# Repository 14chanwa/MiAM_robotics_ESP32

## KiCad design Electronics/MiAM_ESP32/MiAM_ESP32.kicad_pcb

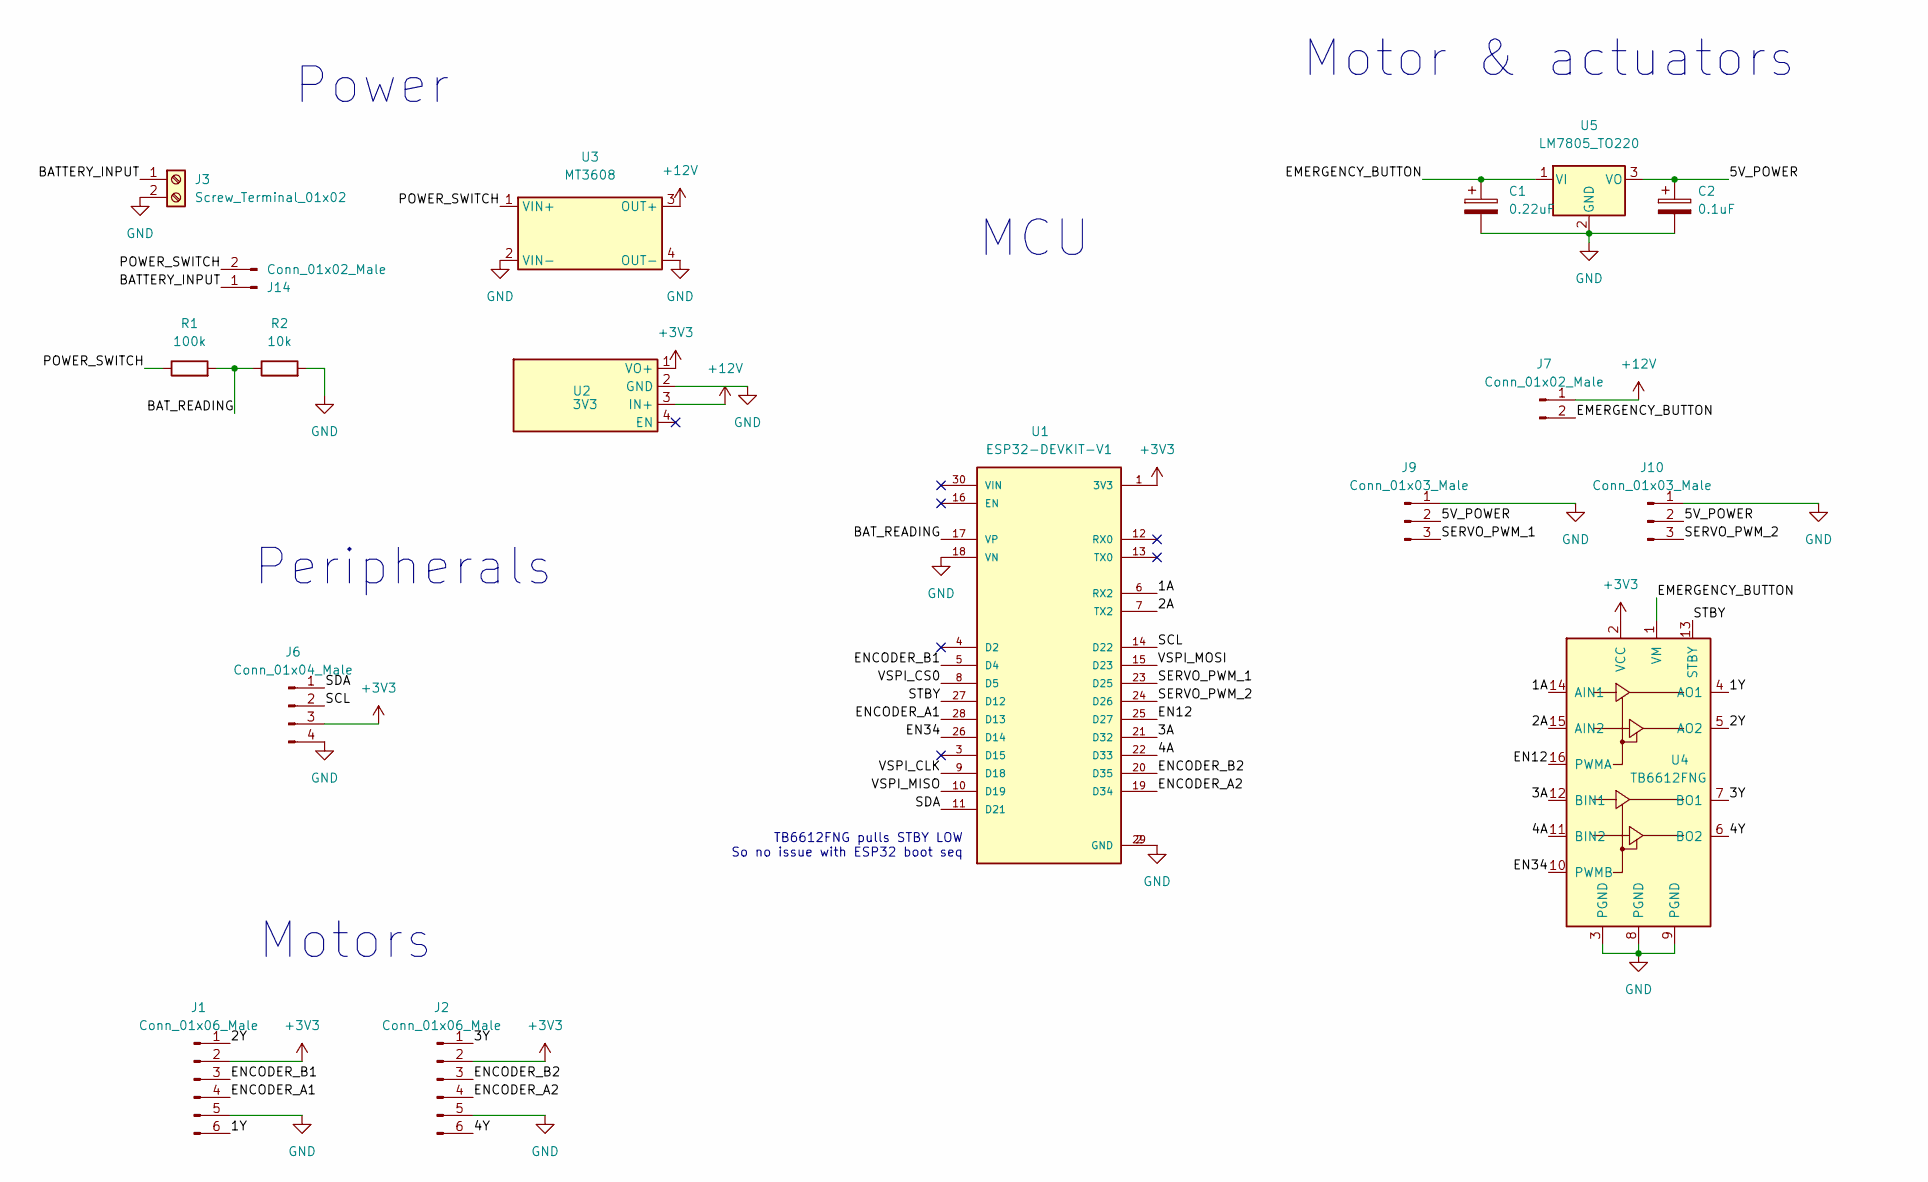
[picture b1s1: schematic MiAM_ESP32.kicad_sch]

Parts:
C1: 0.22uF; CP_Radial_D4.0mm_P2.00mm
C2: 0.1uF; CP_Radial_Tantal_D5.0mm_P5.00mm
J1, J2: Conn_01x06_Male; PinHeader_1x06_P2.54mm_Vertical
J3: Screw_Terminal_01x02; JST_PH_B2B-PH-K_1x02_P2.00mm_Vertical
J6: Conn_01x04_Male; PinHeader_1x04_P2.54mm_Vertical
J7, J14: Conn_01x02_Male; PinHeader_1x02_P2.54mm_Vertical
J9, J10: Conn_01x03_Male; PinHeader_1x03_P2.54mm_Vertical
R1: 100k; R_Axial_DIN0309_L9.0mm_D3.2mm_P12.70mm_Horizontal
R2: 10k; R_Axial_DIN0309_L9.0mm_D3.2mm_P12.70mm_Horizontal
U1: ESP32-DEVKIT-V1; MODULE_ESP32_DEVKIT_V1; PARTREV N/A
U2: 3V3; VoltageRegulator
U3: MT3608
U4: TB6612FNG
U5: LM7805_TO220; TO-220-3_Vertical

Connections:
+3V3: J1.2, J2.2, J6.3, U1.1 (3V3), U2.1 (VO+), U4.2 (VCC)
+12V: J7.1, U2.3 (IN+), U3.3 (OUT+)
/1A: U1.6 (RX2), U4.14 (AIN1)
/1Y: J1.6, U4.4 (AO1)
/2A: U1.7 (TX2), U4.15 (AIN2)
/2Y: J1.1, U4.5 (AO2)
/3A: U1.21 (D32), U4.12 (BIN1)
/3Y: J2.1, U4.7 (BO1)
/4A: U1.22 (D33), U4.11 (BIN2)
/4Y: J2.6, U4.6 (BO2)
/5V_POWER: C2.1, J9.2, J10.2, U5.3 (VO)
/BATTERY_INPUT: J3.1, J14.1
/BAT_READING: R1.2, R2.1, U1.17 (VP)
/EMERGENCY_BUTTON: C1.1, J7.2, U4.1 (VM), U5.1 (VI)
/EN12: U1.25 (D27), U4.16 (PWMA)
/EN34: U1.26 (D14), U4.10 (PWMB)
/ENCODER_A1: J1.4, U1.28 (D13)
/ENCODER_A2: J2.4, U1.19 (D34)
/ENCODER_B1: J1.3, U1.5 (D4)
/ENCODER_B2: J2.3, U1.20 (D35)
/POWER_SWITCH: J14.2, R1.1, U3.1 (VIN+)
/SCL: J6.2, U1.14 (D22)
/SDA: J6.1, U1.11 (D21)
/SERVO_PWM_1: J9.3, U1.23 (D25)
/SERVO_PWM_2: J10.3, U1.24 (D26)
/STBY: U1.27 (D12), U4.13 (STBY)
/VSPI_CLK: U1.9 (D18)
/VSPI_CS0: U1.8 (D5)
/VSPI_MISO: U1.10 (D19)
/VSPI_MOSI: U1.15 (D23)
GND: C1.2, C2.2, J1.5, J2.5, J3.2, J6.4, J9.1, J10.1, R2.2, U1.2 (GND), U1.18 (VN), U1.29 (GND), U2.2 (GND), U3.2 (VIN-), U3.4 (OUT-), U4.3 (PGND), U4.8 (PGND), U4.9 (PGND), U5.2 (GND)

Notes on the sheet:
Motor & actuators
Power
TB6612FNG pulls STBY LOW So no issue with ESP32 boot seq
MCU
Motors
Peripherals

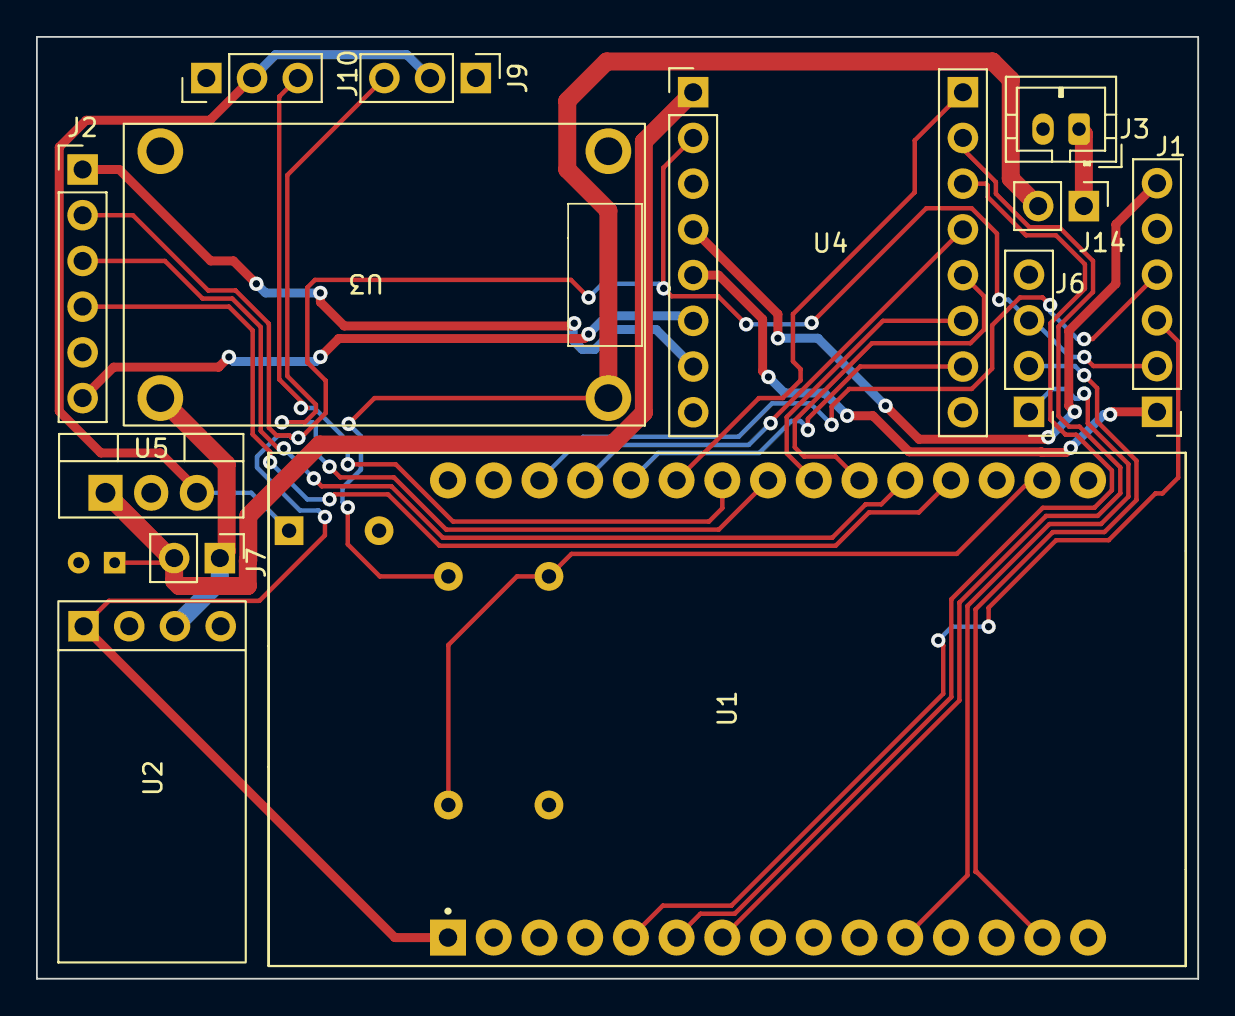
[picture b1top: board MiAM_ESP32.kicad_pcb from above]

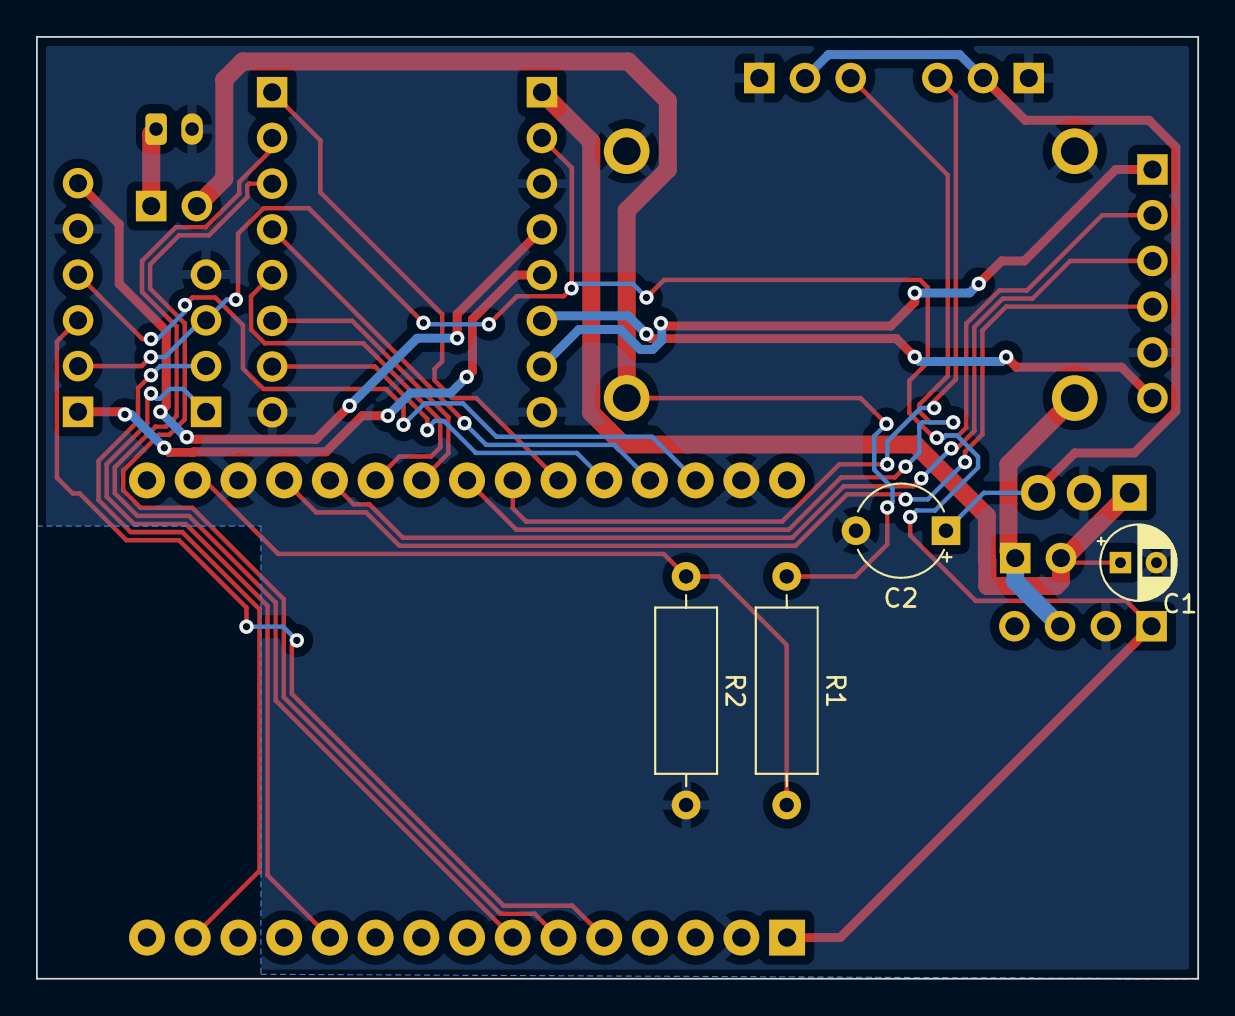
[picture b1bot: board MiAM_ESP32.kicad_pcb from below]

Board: 2 copper layers, 64.5 x 52.3 mm, 17 parts (4 on the bottom side), 27 nets.

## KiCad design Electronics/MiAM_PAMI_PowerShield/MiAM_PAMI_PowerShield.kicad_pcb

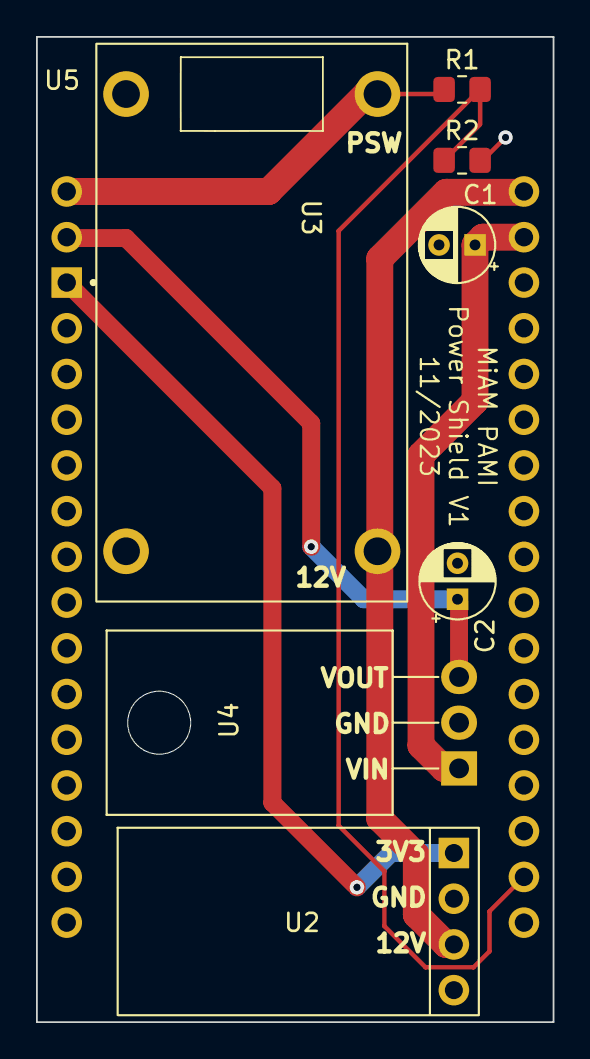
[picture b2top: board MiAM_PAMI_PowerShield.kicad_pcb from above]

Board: 2 copper layers, 28.7 x 54.7 mm, 8 parts (0 on the bottom side), 7 nets.

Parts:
C1: 0.22uF; CP_Radial_D4.0mm_P2.00mm
C2: 0.1uF; CP_Radial_D4.0mm_P2.00mm
R1: 100k; R_0805_2012Metric_Pad1.20x1.40mm_HandSolder
R2: 10k; R_0805_2012Metric_Pad1.20x1.40mm_HandSolder
U2: 3V3; VoltageRegulator
U3: MT3608
U4: LM7805_TO220; TO-220-3_Horizontal_TabDown
U5: ESP32-DEVKIT-V1; ESP32_ShieldPattern

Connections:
+3V3: U2.1 (VO+), U5.1 (3V3)
+12V: U2.3 (IN+), U3.3 (OUT+), U5.SH2 (12V)
/5V_POWER: C2.1, U4.3 (VO), U5.SH3 (SERVO_V)
/BAT_READING: R1.2, R2.1, U5.17 (VP)
/EMERGENCY_BUTTON: C1.1, U4.1 (VI), U5.SH1 (EMG_BUT)
/POWER_SWITCH: R1.1, U3.1 (VIN+), U5.SH4 (POW_SW)
GND: C1.2, C2.2, R2.2, U2.2 (GND), U3.2 (VIN-), U3.4 (OUT-), U4.2 (GND), U5.18 (VN), U5.29 (GND)

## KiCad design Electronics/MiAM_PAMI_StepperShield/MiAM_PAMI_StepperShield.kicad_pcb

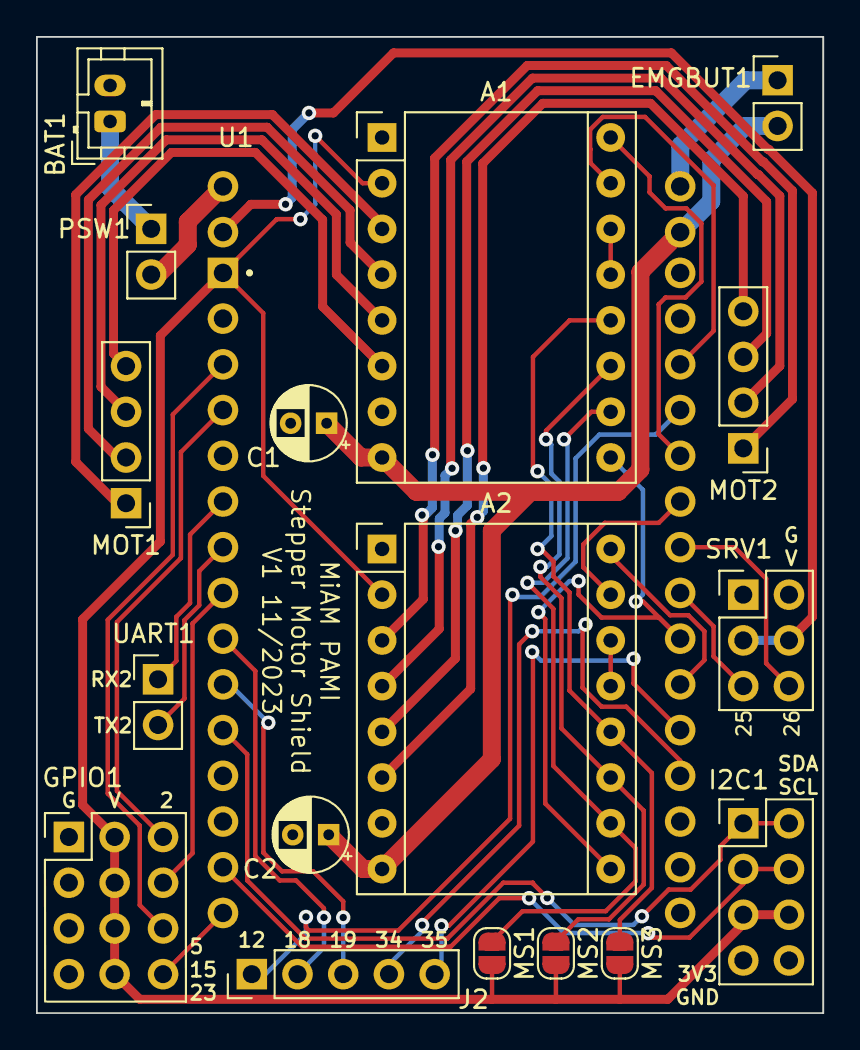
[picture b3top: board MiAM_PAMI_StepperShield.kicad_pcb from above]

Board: 2 copper layers, 43.7 x 54.2 mm, 18 parts (0 on the bottom side), 40 nets.

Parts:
A1, A2: Pololu_Breakout_A4988; Pololu_Breakout-16_15.2x20.3mm
BAT1: Screw_Terminal_01x02; JST_PH_B2B-PH-K_1x02_P2.00mm_Vertical
C1, C2: 100uF; CP_Radial_D4.0mm_P2.00mm
EMGBUT1: Conn_01x02_Male; PinHeader_1x02_P2.54mm_Vertical
GPIO1: PinHeader_3x4_P2.54mm_Vertical
I2C1: Conn_02x04_Odd_Even; PinHeader_2x04_P2.54mm_Vertical
J2: Conn_01x05_Male; PinHeader_1x05_P2.54mm_Vertical
MOT1, MOT2: Conn_01x04_Male; PinHeader_1x04_P2.54mm_Vertical
MS1, MS2, MS3: SolderJumper_2_Open; SolderJumper-2_P1.3mm_Open_RoundedPad1.0x1.5mm
PSW1: Conn_01x02_Male; PinHeader_1x02_P2.54mm_Vertical
SRV1: Conn_02x03_Odd_Even; PinHeader_2x03_P2.54mm_Vertical
U1: ESP32-DEVKIT-V1; ESP32_ShieldPattern
UART1: Conn_01x02_Male; PinHeader_1x02_P2.54mm_Vertical

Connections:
+3V3: A1.2 (VDD), A2.2 (VDD), GPIO1.5, GPIO1.6, GPIO1.7, GPIO1.8, I2C1.5, I2C1.6, MS1.2 (B), MS2.2 (B), MS3.2 (B), U1.1 (3V3)
+12V: EMGBUT1.1, U1.SH2 (12V)
/5V_POWER: SRV1.3, SRV1.4, U1.SH3 (SERVO_V)
/BATTERY_INPUT: BAT1.1, PSW1.1
/DIR_1: A1.16 (DIR), U1.26 (D14)
/DIR_2: A2.16 (DIR), U1.21 (D32)
/EMERGENCY_BUTTON: A1.8 (VMOT), A2.8 (VMOT), C1.1, C2.1, EMGBUT1.2, U1.SH1 (EMG_BUT)
/GPIO2: GPIO1.9, U1.4 (D2)
/GPIO5: GPIO1.10, U1.8 (D5)
/GPIO12: J2.1, U1.27 (D12)
/GPIO15: GPIO1.11, U1.3 (D15)
/GPIO18: J2.2, U1.9 (D18)
/GPIO19: J2.3, U1.10 (D19)
/GPIO23: GPIO1.12, U1.15 (D23)
/GPIO34: J2.4, U1.19 (D34)
/GPIO35: J2.5, U1.20 (D35)
/MS1: A1.10 (MS1), A2.10 (MS1), MS1.1 (A)
/MS2: A1.11 (MS2), A2.11 (MS2), MS2.1 (A)
/MS3: A1.12 (MS3), A2.12 (MS3), MS3.1 (A)
/NOT_MOT_EN: A1.9 (~ENABLE), A2.9 (~ENABLE), U1.22 (D33)
/POWER_SWITCH: PSW1.2, U1.SH4 (POW_SW)
/RX2: U1.6 (RX2), UART1.1
/SCL: I2C1.3, I2C1.4, U1.14 (D22)
/SDA: I2C1.1, I2C1.2, U1.11 (D21)
/SERVO_PWM_1: SRV1.5, U1.23 (D25)
/SERVO_PWM_2: SRV1.6, U1.24 (D26)
/STEP_1: A1.15 (STEP), U1.28 (D13)
/STEP_2: A2.15 (STEP), U1.25 (D27)
/TX2: U1.7 (TX2), UART1.2
GND: A1.1 (GND), A1.7 (GND), A2.1 (GND), A2.7 (GND), BAT1.2, C1.2, C2.2, GPIO1.1, GPIO1.2, GPIO1.3, GPIO1.4, I2C1.7, I2C1.8, SRV1.1, SRV1.2, U1.2 (GND), U1.18 (VN), U1.29 (GND)
unnamed: A1.4 (1A), MOT1.2
unnamed: A1.3 (1B), MOT1.1
unnamed: A1.5 (2A), MOT1.3
unnamed: A1.6 (2B), MOT1.4
unnamed: A1.13 (~RESET), A1.14 (~SLEEP)
unnamed: A2.4 (1A), MOT2.2
unnamed: A2.3 (1B), MOT2.1
unnamed: A2.5 (2A), MOT2.3
unnamed: A2.6 (2B), MOT2.4
unnamed: A2.13 (~RESET), A2.14 (~SLEEP)

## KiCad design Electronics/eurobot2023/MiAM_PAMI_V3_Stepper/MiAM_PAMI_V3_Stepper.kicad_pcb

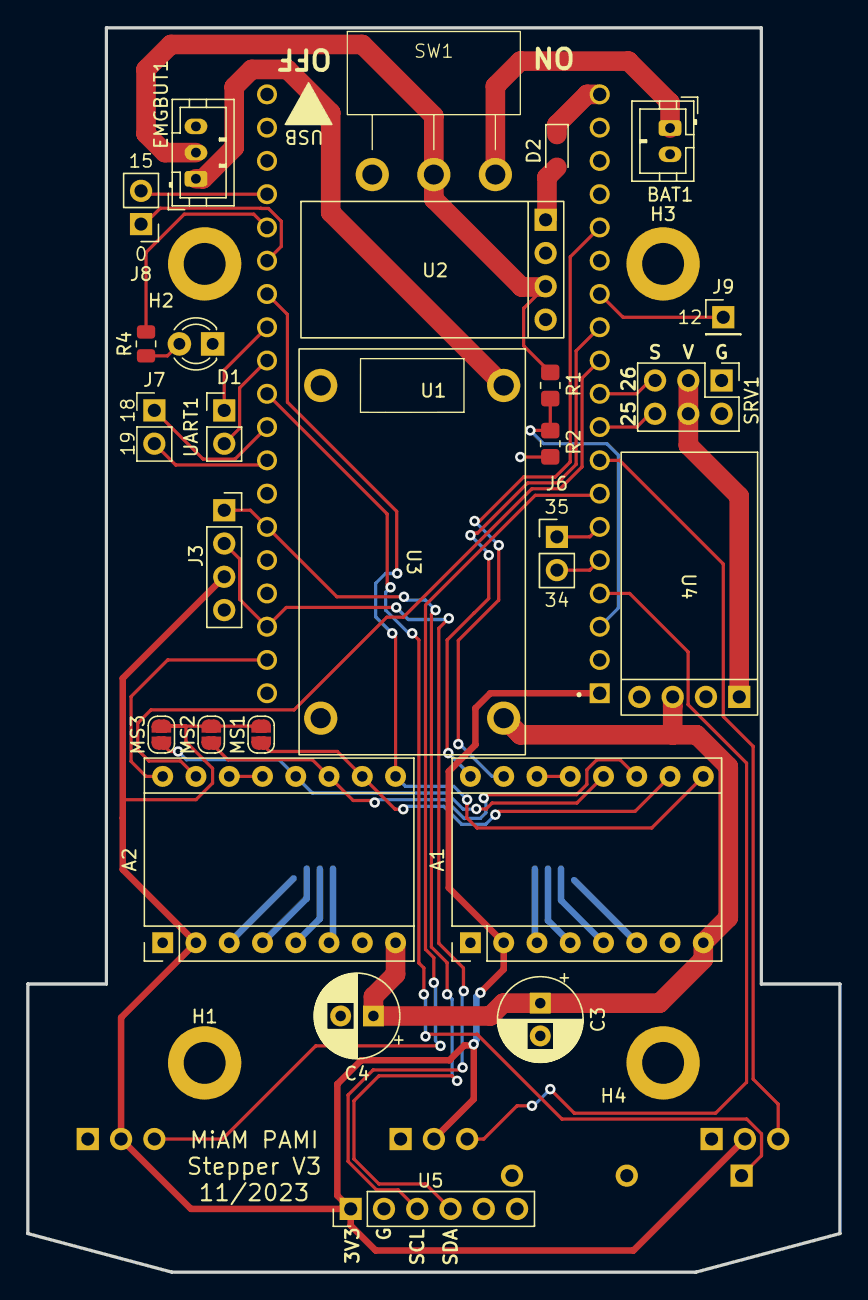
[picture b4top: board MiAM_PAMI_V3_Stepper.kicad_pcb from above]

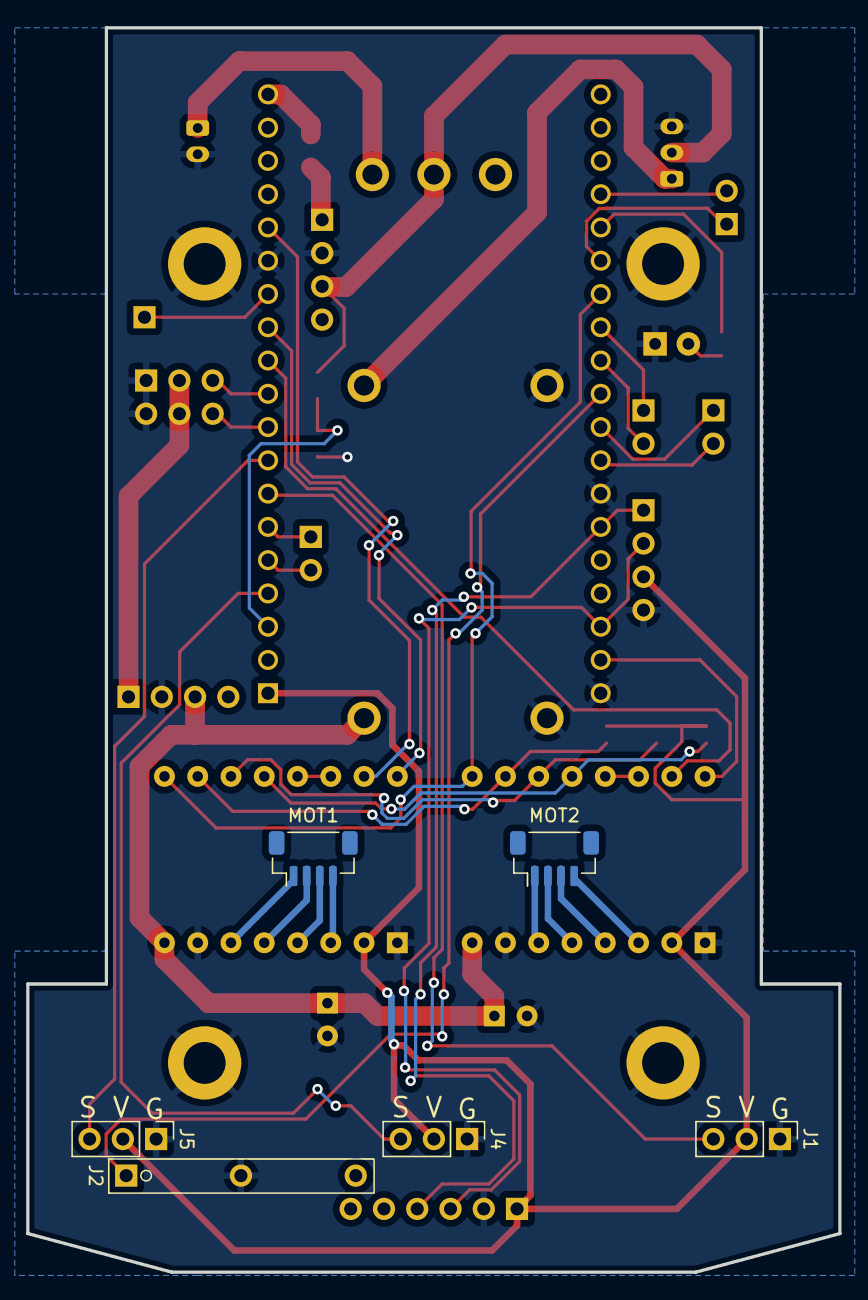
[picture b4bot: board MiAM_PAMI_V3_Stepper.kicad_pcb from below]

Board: 2 copper layers, 62.0 x 95.0 mm, 37 parts (6 on the bottom side), 47 nets.

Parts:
A1, A2: Pololu_Breakout_A4988; Pololu_Breakout-16_15.2x20.3mm
BAT1: Screw_Terminal_01x02; JST_PH_B2B-PH-K_1x02_P2.00mm_Vertical
C3, C4: 100uF; CP_Radial_D6.3mm_P2.50mm
D1: LED; LED_D3.0mm
D2: D_Schottky; D_SOD-323_HandSoldering
EMGBUT1: Conn_01x02_Male; JST_PH_B3B-PH-K_1x03_P2.00mm_Vertical
H1, H2, H3, H4: MountingHole_Pad; MountingHole_3.2mm_M3_DIN965_Pad
J1, J4, J5: TCRT5000L_Breakout
J2: Conn_01x03_Male; Microruptor
J3: SSD1306_vertical
J6, J7, J8: Conn_01x02_Pin; PinHeader_1x02_P2.54mm_Vertical
J9: Conn_01x01_Pin; PinHeader_1x01_P2.54mm_Vertical
MOT1, MOT2: Conn_01x04_Male; JST_SH_BM04B-SRSS-TB_1x04-1MP_P1.00mm_Vertical
MS1, MS2, MS3: SolderJumper_2_Open; SolderJumper-2_P1.3mm_Open_RoundedPad1.0x1.5mm
R1: 100k; R_0805_2012Metric_Pad1.20x1.40mm_HandSolder
R2: 10k; R_0805_2012Metric_Pad1.20x1.40mm_HandSolder
R4: 200; R_0805_2012Metric
SRV1: Conn_02x03_Odd_Even; PinHeader_2x03_P2.54mm_Vertical
SW1: SW_DPDT_x2; SS-12D11
U1: ESP32-DEVKITC-32U; ESP32U-ShieldPattern
U2, U4: 5V; VoltageRegulator
U3: MT3608
U5: PinHeader_1x06_P2.54mm_Vertical
UART1: Conn_01x02_Male; PinHeader_1x02_P2.54mm_Vertical

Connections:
+3V3: A1.2 (VDD), A2.2 (VDD), J1.2 (V), J3.3 (VCC), J4.2 (V), J5.2 (V), MS1.2 (B), MS2.2 (B), MS3.2 (B), U1.1 (3V3), U5.1 (VIN)
+12V: A1.8 (VMOT), A2.8 (VMOT), C3.1, C4.1, U3.3 (OUT+), U4.3 (IN+)
/5V_BOARD: D2.2 (A), U2.1 (VO+)
/5V_POWER: SRV1.3, SRV1.4, U4.1 (VO+)
/BATTERY_INPUT: BAT1.1, SW1.3 (C)
/BAT_READING: R1.2, R2.1, U1.3 (SENSOR_VP)
/DIR_1: A1.16 (DIR), U1.12 (IO14)
/DIR_2: A2.16 (DIR), U1.37 (IO23)
/EMERGENCY_BUTTON: EMGBUT1.1, U3.1 (VIN+)
/GPIO0: J8.1, U1.25 (IO0)
/GPIO2: R4.2, U1.24 (IO2)
/GPIO5: J2.1, U1.29 (IO5)
/GPIO12: J9.1, U1.13 (IO12)
/GPIO15: J8.2, U1.23 (IO15)
/GPIO18: J7.1, U1.30 (IO18)
/GPIO19: J7.2, U1.31 (IO19)
/GPIO34: J6.2, U1.5 (IO34)
/GPIO35: J6.1, U1.6 (IO35)
/MS1: A1.10 (MS1), A2.10 (MS1), MS1.1 (A)
/MS2: A1.11 (MS2), A2.11 (MS2), MS2.1 (A)
/MS3: A1.12 (MS3), A2.12 (MS3), MS3.1 (A)
/NOT_MOT_EN: A1.9 (~ENABLE), A2.9 (~ENABLE), U1.26 (IO4)
/POWER_SWITCH: EMGBUT1.2, R1.1, SW1.2 (B), U2.3 (IN+)
/RX2: U1.27 (IO16), UART1.1
/SCL: J3.2 (SCL), U1.36 (IO22), U5.3 (SCL)
/SDA: J3.1 (SDA), U1.33 (IO21), U5.4 (SDA)
/SERVO_PWM_1: SRV1.6, U1.9 (IO25)
/SERVO_PWM_2: SRV1.5, U1.10 (IO26)
/STEP_1: A1.15 (STEP), U1.15 (IO13)
/STEP_2: A2.15 (STEP), U1.11 (IO27)
/TCRT0: J1.3 (S), U1.7 (IO32)
/TCRT1: J4.3 (S), U1.4 (SENSOR_VN)
/TCRT2: J5.3 (S), U1.8 (IO33)
/TX2: U1.28 (IO17), UART1.2
GND: A1.1 (GND), A1.7 (GND), A2.1 (GND), A2.7 (GND), BAT1.2, C3.2, C4.2, D1.1 (K), EMGBUT1.3, H1.1, H2.1, H3.1, H4.1, J1.1 (G), J2.2, J3.4 (GND), J4.1 (G), J5.1 (G), R2.2, SRV1.1, SRV1.2, U1.14 (GND1), U1.32 (GND2), U1.38 (GND3), U2.2 (GND), U3.2 (VIN-), U3.4 (OUT-), U4.2 (GND), U5.2 (GND)
unnamed: A1.4 (1A), MOT1.3
unnamed: A1.3 (1B), MOT1.4
unnamed: A1.5 (2A), MOT1.2
unnamed: A1.6 (2B), MOT1.1
unnamed: A1.13 (~RESET), A1.14 (~SLEEP)
unnamed: A2.4 (1A), MOT2.3
unnamed: A2.3 (1B), MOT2.4
unnamed: A2.5 (2A), MOT2.2
unnamed: A2.6 (2B), MOT2.1
unnamed: A2.13 (~RESET), A2.14 (~SLEEP)
unnamed: D1.2 (A), R4.1
unnamed: D2.1 (K), U1.19 (EXT_5V)
